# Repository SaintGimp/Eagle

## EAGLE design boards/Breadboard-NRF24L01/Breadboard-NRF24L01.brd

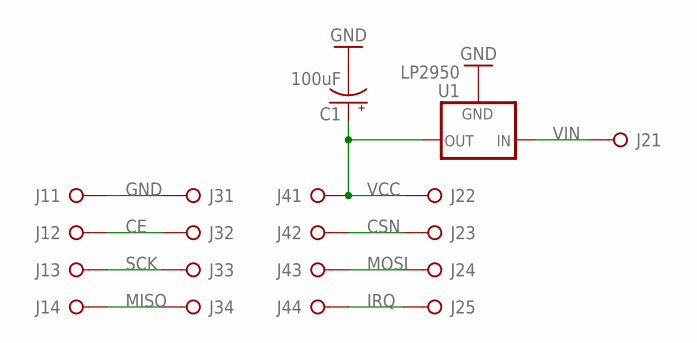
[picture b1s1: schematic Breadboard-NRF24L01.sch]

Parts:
C1: 100uF; CAP-POL-2.5-6
J1, J3, J4: PINHD-1X4; 1X04
J2: PINHD-1X5; 1X05
U1: LP2950; TO92-INLINE

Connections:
CE: J1.2, J3.2
CSN: J2.3, J4.2
GND: C1.-, J1.1, J3.1, U1.2 (GND)
IRQ: J2.5, J4.4
MISO: J1.4, J3.4
MOSI: J2.4, J4.3
SCK: J1.3, J3.3
VCC: C1.+, J2.2, J4.1, U1.1 (OUT)
VIN: J2.1, U1.3 (IN)

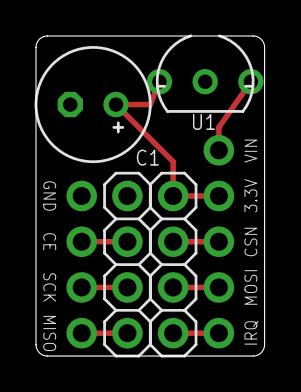
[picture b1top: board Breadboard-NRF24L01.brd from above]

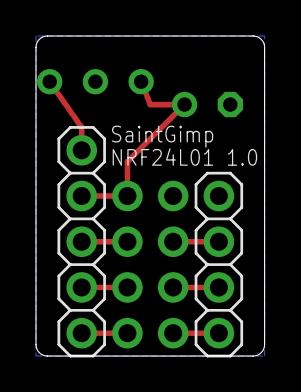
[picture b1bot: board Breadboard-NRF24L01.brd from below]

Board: 2 copper layers, 12.7 x 17.8 mm, 6 parts (2 on the bottom side), 9 nets.

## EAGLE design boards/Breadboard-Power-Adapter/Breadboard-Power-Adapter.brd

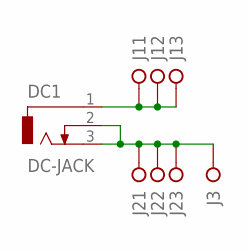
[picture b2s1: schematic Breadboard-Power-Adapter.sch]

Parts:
DC1: DC-JACK
J1, J2: PINHD-1X3; 1X03
J3: PINHD-1X1; 1X01

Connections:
GND: DC1.2, DC1.3, J2.1, J2.2, J2.3, J3.1
VCC: DC1.1, J1.1, J1.2, J1.3

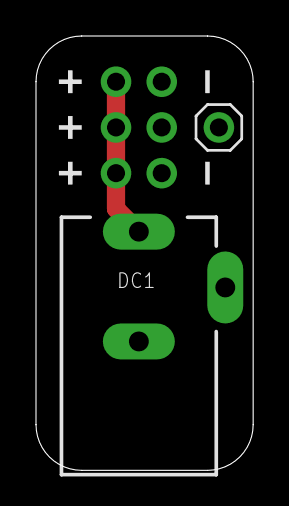
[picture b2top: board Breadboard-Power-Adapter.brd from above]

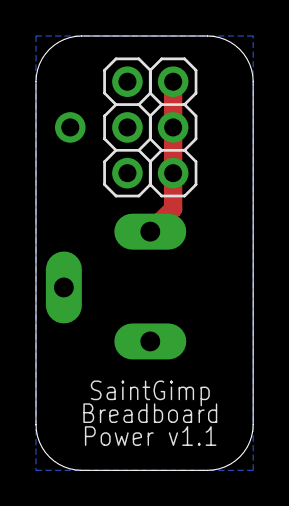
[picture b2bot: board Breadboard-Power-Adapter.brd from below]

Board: 2 copper layers, 12.1 x 24.1 mm, 4 parts (2 on the bottom side), 2 nets.

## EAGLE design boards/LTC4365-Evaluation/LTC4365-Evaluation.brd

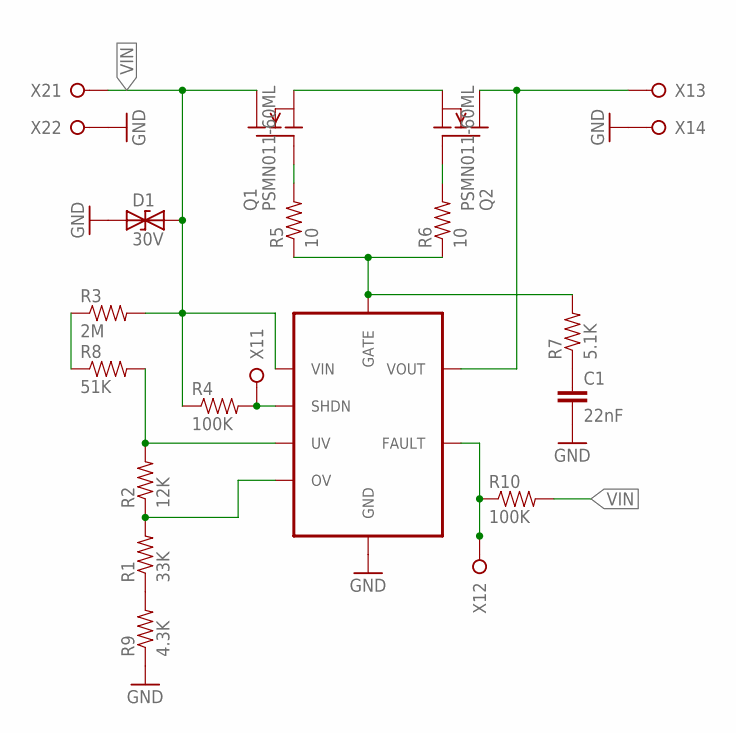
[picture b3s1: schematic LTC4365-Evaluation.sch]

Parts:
C1: 22nF; CAPACITOR-0805
D1: 30V; TVS-DO-201
IC1: LTC4365; SOT-23-8
Q1, Q2: PSMN011-60ML; LFPAK33
R1: 33K; RESISTOR-0805
R2: 12K; RESISTOR-0805
R3: 2M; RESISTOR-0805
R4, R10: 100K; RESISTOR-0805
R5: 10; AXIAL-7.5MM
R6: 10; RESISTOR-0805
R7: 5.1K; RESISTOR-0805
R8: 51K; RESISTOR-0805
R9: 4.3K; RESISTOR-0805
X1: SCREW-TERM-4
X2: SCREW-TERM-2

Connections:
GND: C1.2, D1.1, IC1.4 (GND), R9.1, X1.4, X2.2
unnamed: Q1.4 (GATE), R5.P$2 (2)
unnamed: Q2.4 (GATE), R6.2
unnamed: IC1.8 (GATE), R5.P$1 (1), R6.1, R7.2
unnamed: Q1.1 (SRC), Q1.2 (SRC), Q1.3 (SRC), Q2.1 (SRC), Q2.2 (SRC), Q2.3 (SRC)
unnamed: IC1.7 (VOUT), Q2.MB (DRN), X1.3
unnamed: C1.1, R7.1
unnamed: IC1.6 (FAULT), R10.1, X1.2
unnamed: IC1.5 (SHDN), R4.2, X1.1
unnamed: R3.1, R8.1
unnamed: IC1.2 (UV), R2.2, R8.2
unnamed: R1.1, R9.2
unnamed: IC1.3 (OV), R1.2, R2.1
VIN: D1.2, IC1.1 (VIN), Q1.MB (DRN), R3.2, R4.1, R10.2, X2.1

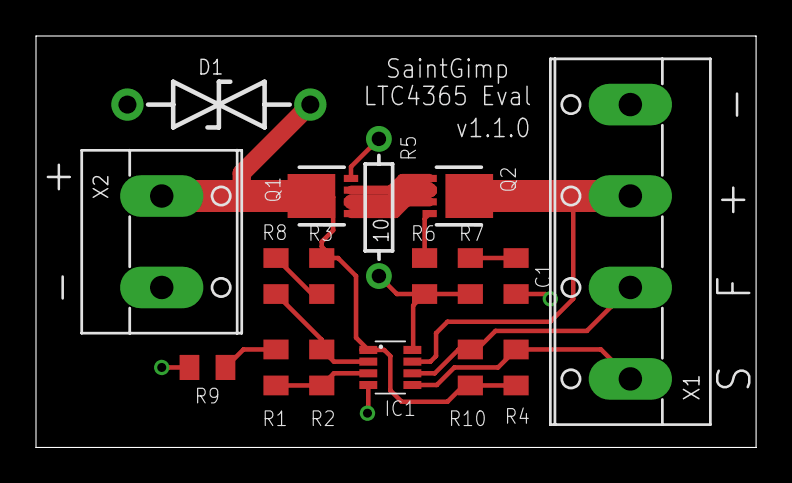
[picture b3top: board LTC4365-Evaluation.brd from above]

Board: 2 copper layers, 40.0 x 22.9 mm, 17 parts (0 on the bottom side), 14 nets.

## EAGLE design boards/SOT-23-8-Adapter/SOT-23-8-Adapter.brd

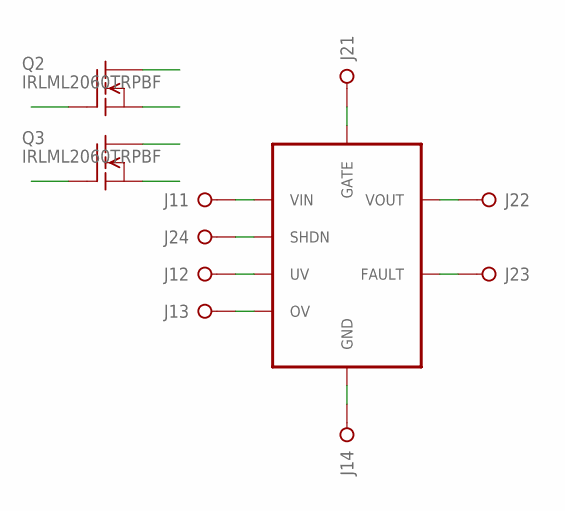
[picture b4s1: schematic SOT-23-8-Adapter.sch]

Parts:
J1, J2: PINHD-1X4; 1X04
Q1: LTC4365; SOT-23-8
Q2, Q3: IRLML2060TRPBF; SOT-23-3

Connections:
1-1: J1.1, Q1.1 (VIN), Q2.2 (SRC)
1-2: J1.2, Q1.2 (UV), Q2.1 (GATE)
1-3: J1.3, Q1.3 (OV), Q3.2 (SRC)
1-4: J1.4, Q1.4 (GND), Q3.1 (GATE)
2-1: J2.1, Q1.8 (GATE), Q2.3 (DRN)
2-2: J2.2, Q1.7 (VOUT)
2-3: J2.3, Q1.6 (FAULT)
2-4: J2.4, Q1.5 (SHDN), Q3.3 (DRN)

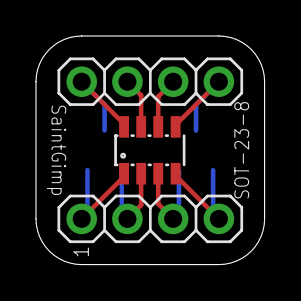
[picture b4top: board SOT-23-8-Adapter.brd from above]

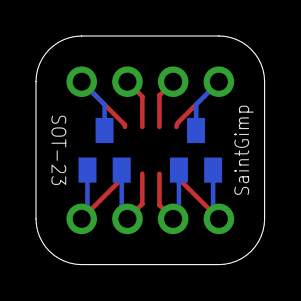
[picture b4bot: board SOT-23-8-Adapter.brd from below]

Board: 2 copper layers, 12.7 x 12.7 mm, 5 parts (2 on the bottom side), 8 nets.

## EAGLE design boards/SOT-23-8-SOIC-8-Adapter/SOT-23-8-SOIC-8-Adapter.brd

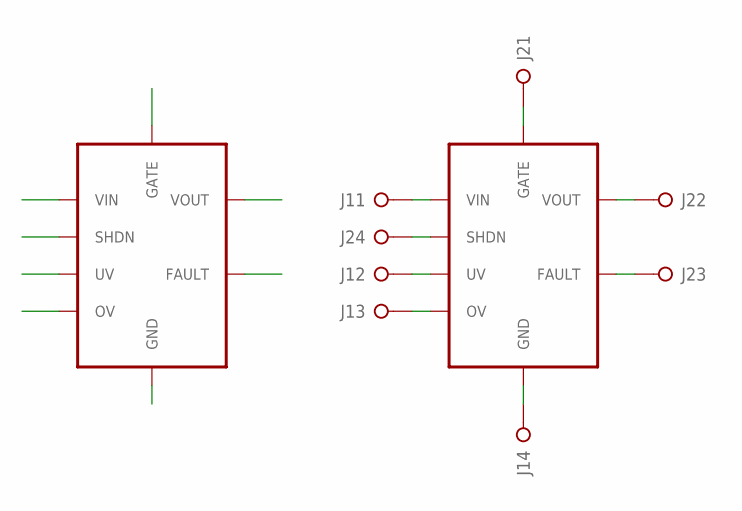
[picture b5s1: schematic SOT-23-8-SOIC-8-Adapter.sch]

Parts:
J1, J2: PINHD-1X4; 1X04
Q1: LTC4365; SOT-23-8
U$1: DUMMY1; SOIC-08

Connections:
1-1: J1.1, Q1.1 (VIN), U$1.1 (VIN)
1-2: J1.2, Q1.2 (UV), U$1.2 (UV)
1-3: J1.3, Q1.3 (OV), U$1.3 (OV)
1-4: J1.4, Q1.4 (GND), U$1.4 (GND)
2-1: J2.1, Q1.8 (GATE), U$1.8 (GATE)
2-2: J2.2, Q1.7 (VOUT), U$1.7 (VOUT)
2-3: J2.3, Q1.6 (FAULT), U$1.6 (FAULT)
2-4: J2.4, Q1.5 (SHDN), U$1.5 (SHDN)

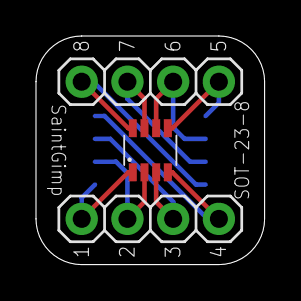
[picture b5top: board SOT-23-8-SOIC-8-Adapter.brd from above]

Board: 2 copper layers, 12.7 x 12.7 mm, 4 parts (1 on the bottom side), 8 nets.
